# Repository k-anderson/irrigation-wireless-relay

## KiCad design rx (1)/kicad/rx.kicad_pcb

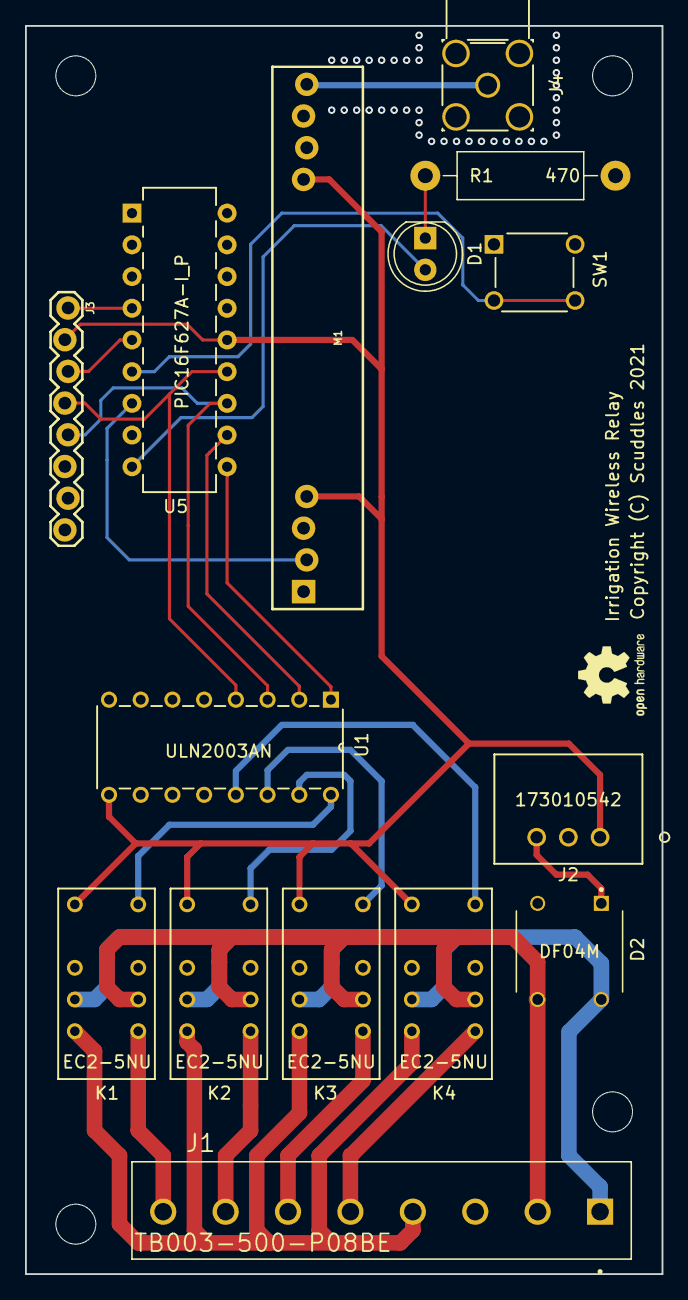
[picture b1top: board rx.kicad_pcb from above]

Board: 2 copper layers, 51.0 x 100.0 mm, 15 parts (0 on the bottom side), 24 nets.

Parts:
D1: LED; LED_D5.0mm
D2: DF04M
J1: TB003-500-P08BE; CUI_TB003-500-P08BE
J2: 173010542
J3: CONN_08LOCK; 1X08_LOCK
J4: RF2-03E-T-00-50-G
K1, K2, K3, K4: EC2-5NU
M1: RF-LINK_RX
R1: 470; R_Axial_DIN0411_L9.9mm_D3.6mm_P15.24mm_Horizontal
SW1: 1825910-6
U1: ULN2003AN
U5: PIC16F627A-I_P; PIC16F627A-I&slash_P

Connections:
/Logic/Button: SW1.3, SW1.4, U5.6
/Logic/Data: M1.DATA, U5.7
/Logic/LED: D1.2, U5.9
/Power Supply/AC_LINE: D2.3, J1.2, K1.6, K2.6, K3.6, K4.6
/Power Supply/AC_NEUTRAL: D2.4, J1.1, K1.3, K2.3, K3.3, K4.3
/Switching/COM: J1.4, K1.4, K2.4, K3.4, K4.4
/Switching/IN_1: U1.1, U5.10
/Switching/IN_2: U1.2, U5.11
/Switching/IN_3: J3.5, U1.3, U5.12
/Switching/IN_4: J3.4, U1.4, U5.13
/Switching/OUT_1: J1.8, K1.5
/Switching/OUT_2: J1.7, K2.5
/Switching/OUT_3: J1.6, K3.5
/Switching/OUT_4: J1.5, K4.5
unnamed: D1.1, R1.1
unnamed: D2.1, J2.1
unnamed: J3.1, U5.4
unnamed: J4.1, M1.ANT
unnamed: K1.8, U1.16
unnamed: K2.8, U1.15
unnamed: K3.8, U1.14
unnamed: K4.8, U1.13
Vdd: J2.3, J3.2, K1.1, K2.1, K3.1, K4.1, M1.+5V@, U1.9, U5.14
Vss: D2.2, J2.2, J3.3, J4.2, J4.3, J4.4, J4.5, M1.GND@, R1.2, SW1.1, SW1.2, U1.8, U5.5

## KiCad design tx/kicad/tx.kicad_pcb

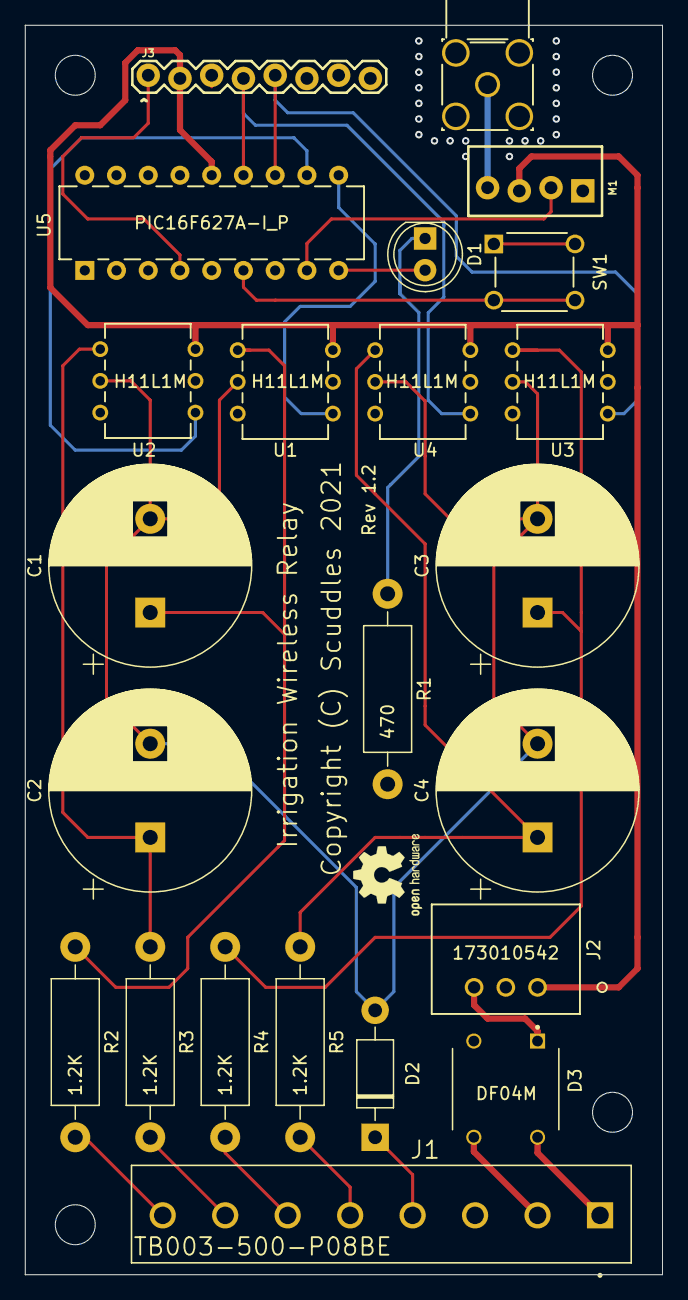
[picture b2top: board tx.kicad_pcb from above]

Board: 2 copper layers, 51.0 x 100.0 mm, 23 parts (0 on the bottom side), 25 nets.

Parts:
C1, C2, C3, C4: 470uF; CP_Radial_D16.0mm_P7.50mm
D1: LED; LED_D5.0mm
D2: D; D_DO-41_SOD81_P10.16mm_Horizontal
D3: DF04M
J1: TB003-500-P08BE; CUI_TB003-500-P08BE
J2: 173010542
J3: CONN_08LOCK; 1X08_LOCK
J4: RF2-03E-T-00-50-G
M1: RF-LINK_TX; WRL-10534
R1: 470; R_Axial_DIN0411_L9.9mm_D3.6mm_P15.24mm_Horizontal
R2, R3, R4, R5: 1.2K; R_Axial_DIN0411_L9.9mm_D3.6mm_P15.24mm_Horizontal
SW1: 1825910-6
U1, U2, U3, U4: H11L1M
U5: PIC16F627A-I_P; PIC16F627A-I&slash_P

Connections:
/Logic/Button: SW1.3, SW1.4, U5.6
/Logic/Data: M1.DATA, U5.8
/Logic/LED: D1.2, U5.9
/Power Supply/AC_LINE: D3.3, J1.2
/Power Supply/AC_NEUTRAL: D3.4, J1.1
/Signal Conditioner/COM: D2.1, J1.4
/Signal Conditioner/IN_1: J1.8, R2.2
/Signal Conditioner/IN_2: J1.7, R3.2
/Signal Conditioner/IN_3: J1.6, R4.2
/Signal Conditioner/IN_4: J1.5, R5.2
/Signal Conditioner/OUT_1: U1.4, U5.10
/Signal Conditioner/OUT_2: U2.4, U5.11
/Signal Conditioner/OUT_3: J3.5, U3.4, U5.12
/Signal Conditioner/OUT_4: J3.4, U4.4, U5.13
unnamed: C1.1, R2.1, U1.1
unnamed: C1.2, C2.2, C3.2, C4.2, D2.2, U1.2, U2.2, U3.2, U4.2
unnamed: C2.1, R3.1, U2.1
unnamed: C3.1, R4.1, U3.1
unnamed: C4.1, R5.1, U4.1
unnamed: D1.1, R1.1
unnamed: D3.1, J2.1
unnamed: J3.1, U5.4
unnamed: J4.1, M1.ANT
Vdd: J2.3, J3.2, M1.VCC, U1.6, U2.6, U3.6, U4.6, U5.14
Vss: D3.2, J2.2, J3.3, J4.2, J4.3, J4.4, J4.5, M1.GND, R1.2, SW1.1, SW1.2, U1.5, U2.5, U3.5, U4.5, U5.5

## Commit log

2021-01-27 preparing plots
2021-01-27 update plots
2021-01-27 wong plot name
2021-01-27 rebuild the plots
2021-01-31 update prototype pics

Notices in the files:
rx (1)/kicad/rx.kicad_pcb:
Copyright (C) Scuddles 2021
parts and their libraries:
Copyright 2016 Accelerated Designs. All rights reserved.
